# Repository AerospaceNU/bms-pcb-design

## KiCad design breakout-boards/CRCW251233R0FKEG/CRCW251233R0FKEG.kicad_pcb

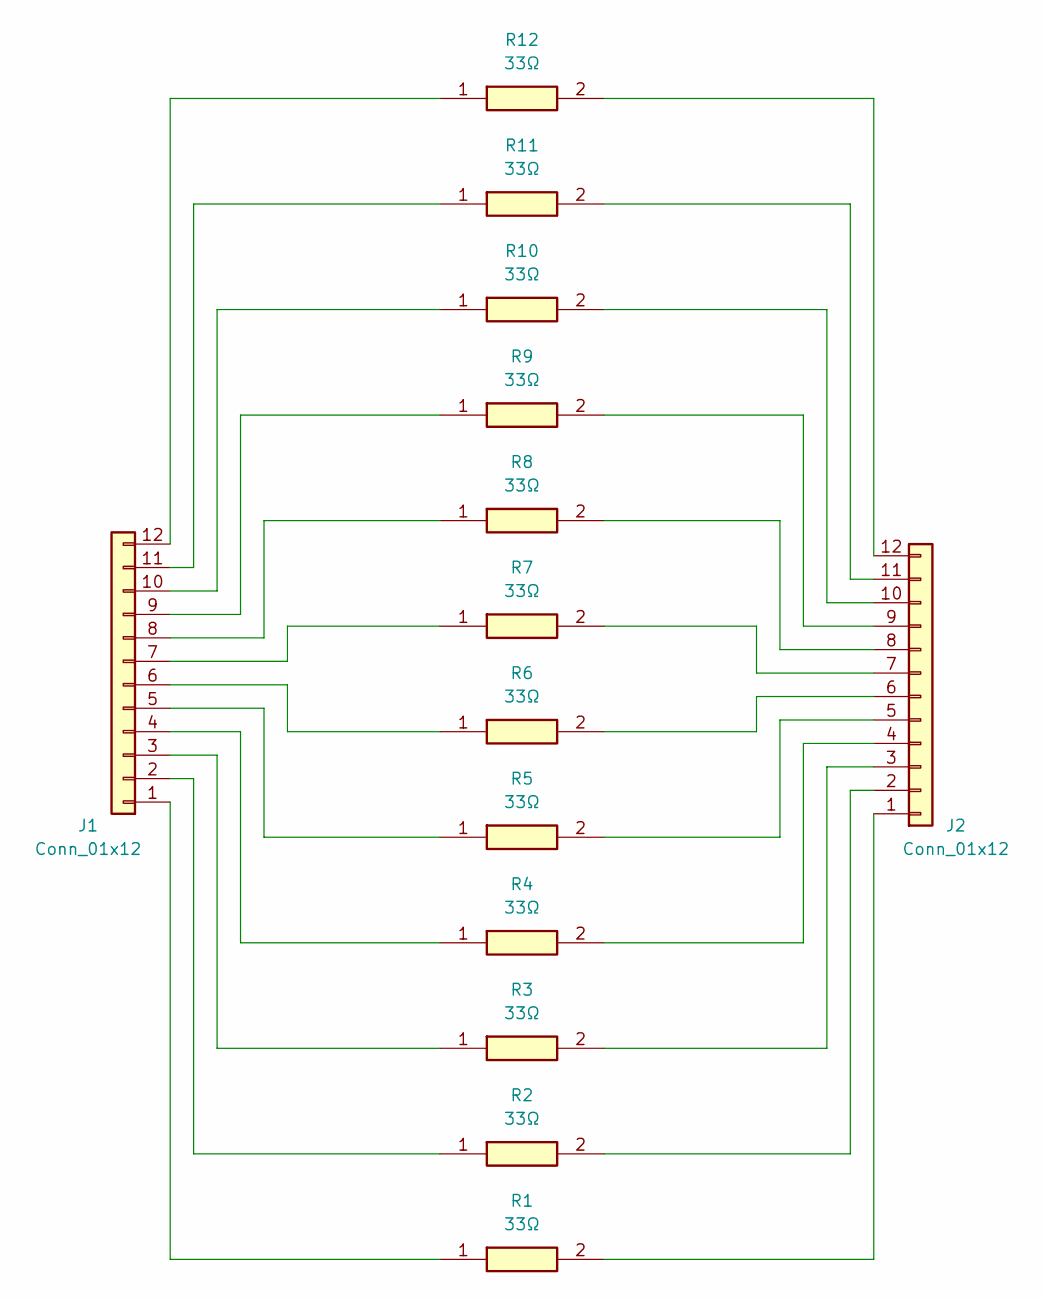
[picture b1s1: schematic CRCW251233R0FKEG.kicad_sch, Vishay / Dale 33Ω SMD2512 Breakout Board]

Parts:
J1, J2: Conn_01x12; PinSocket_1x12_P2.54mm_Vertical
R1, R2, R3, R4, R5, R6, R7, R8, R9, R10, R11, R12: 33Ω; RESC6332X70N; Manufacturer_Part_Number CRCW251233R0FKEG

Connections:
unnamed: J1.1, R1.1
unnamed: J1.2, R2.1
unnamed: J1.3, R3.1
unnamed: J1.4, R4.1
unnamed: J1.5, R5.1
unnamed: J1.6, R6.1
unnamed: J1.7, R7.1
unnamed: J1.8, R8.1
unnamed: J1.9, R9.1
unnamed: J1.10, R10.1
unnamed: J1.11, R11.1
unnamed: J1.12, R12.1
unnamed: J2.1, R1.2
unnamed: J2.2, R2.2
unnamed: J2.3, R3.2
unnamed: J2.4, R4.2
unnamed: J2.5, R5.2
unnamed: J2.6, R6.2
unnamed: J2.7, R7.2
unnamed: J2.8, R8.2
unnamed: J2.9, R9.2
unnamed: J2.10, R10.2
unnamed: J2.11, R11.2
unnamed: J2.12, R12.2

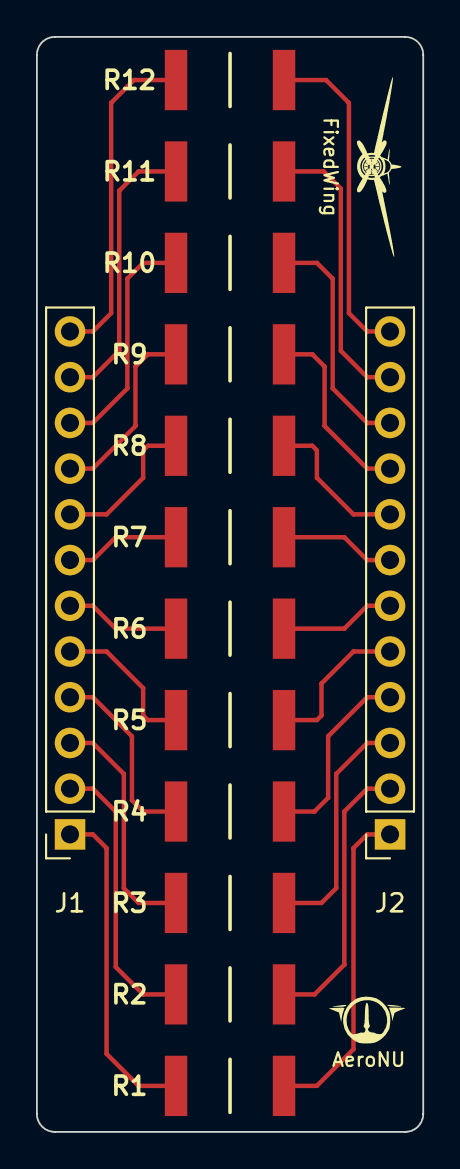
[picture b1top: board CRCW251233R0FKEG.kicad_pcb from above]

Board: 2 copper layers, 21.5 x 60.8 mm, 16 parts (0 on the bottom side), 24 nets.

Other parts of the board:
AeroNU: LOGO; AeroNU - Logo (Smol)
FixedWing: LOGO; FixedWing - Logo (Smol)

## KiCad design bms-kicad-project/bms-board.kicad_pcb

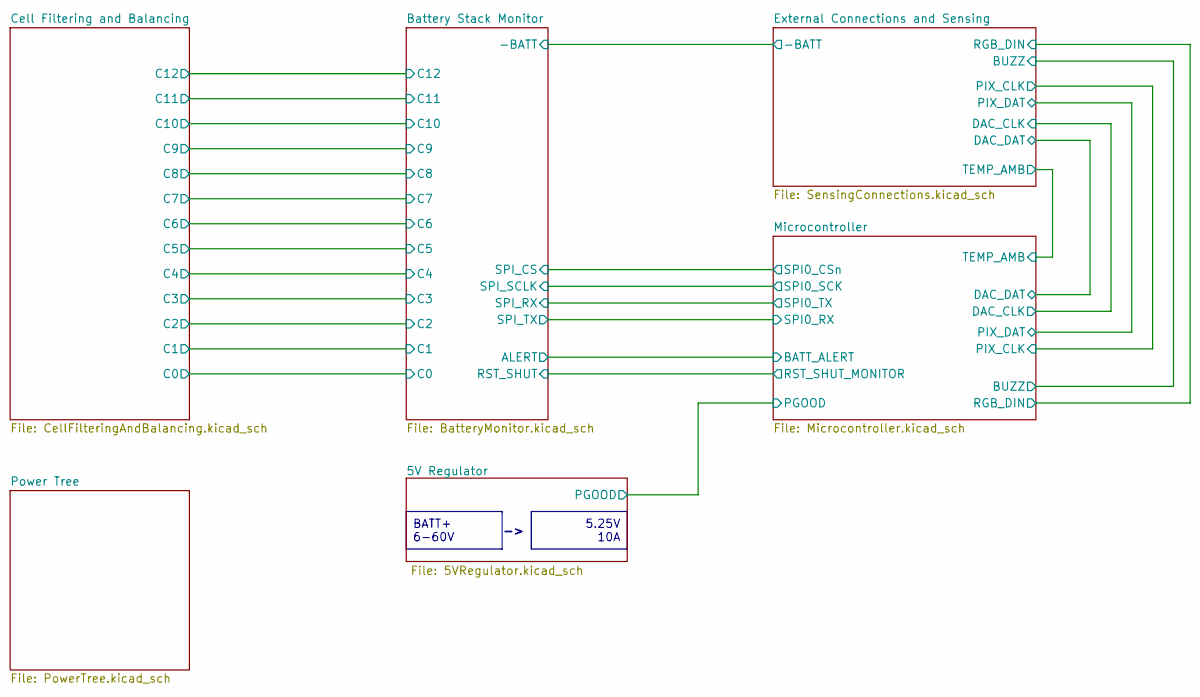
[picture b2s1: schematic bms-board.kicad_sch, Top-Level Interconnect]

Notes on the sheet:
BATT+ 6-60V
5.25V 10A

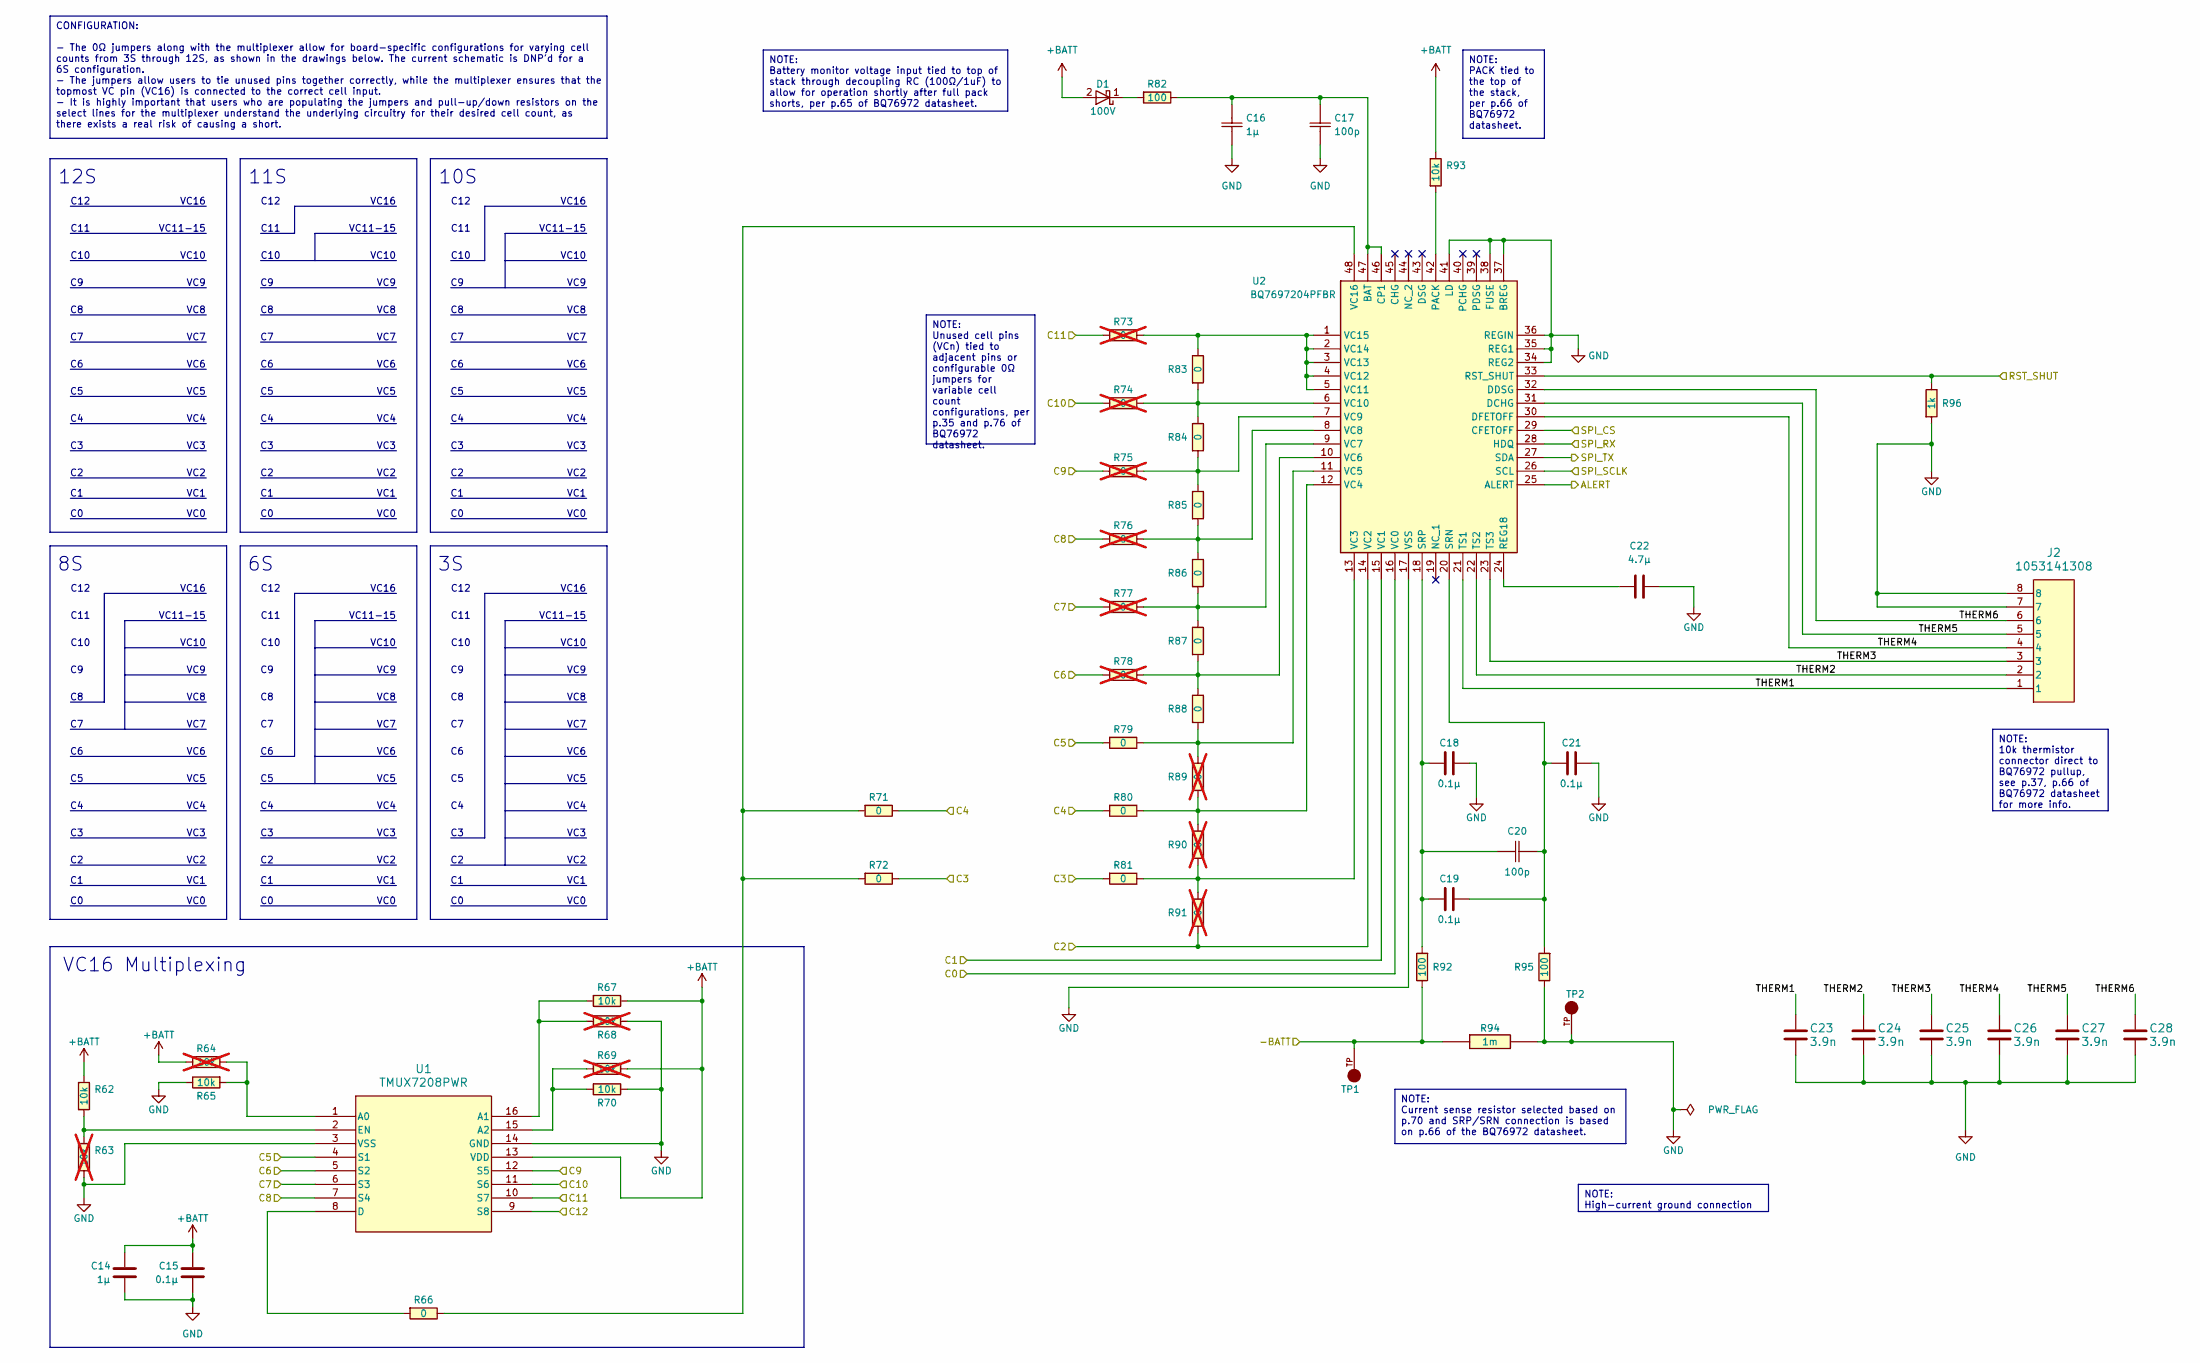
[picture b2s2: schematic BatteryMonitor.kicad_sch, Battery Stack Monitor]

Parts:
C14: 1µ; CAPC1608X90N; Manufacturer Part Number GCM188R71C105KA64D
C15, C18, C19, C21: 0.1µ; CAP_GCJ-18_MUR; Manufacturer Part Number GCJ188R72A104KA01D
C16: 1µ; CAP_CL31_SAM; Manufacturer Part Number CL31B105KCHNNNE
C17, C20: 100p; CAPC220145_88N_KEM; Manufacturer Part Number C0805C101J1GACTU
C22: 4.7µ; CAPC2012X145N; Manufacturer Part Number GCM21BC71E475KE36L
C23, C24, C25, C26, C27, C28: 3.9n; G-21_MUR; Manufacturer Part Number GRM2165C1H392JA01D
D1: 100V; D_SOD-123; Manufacturer Part Number BAS100AS_R1_00001
J2: 1053141308; CONN_SD-105314-100_08_MOL; Manufacturer Part Number 1053141308
R62, R65, R67, R70, R93: 10k; KOA_Speer-RK73H2A-0-0-MFG; power rating 0.125W; tolerance 1%; Manufacturer Part Number RK73H2ATTD1002F; digikey description RES 10K OHM 1% 1/4W 0805
R63, R64, R68, R69: 10k; KOA_Speer-RK73H2A-0-0-MFG; power rating 0.125W; tolerance 1%; Manufacturer Part Number RK73H2ATTD1002F; digikey description RES 10K OHM 1% 1/4W 0805; not fitted
R66, R71, R72, R79, R80, R81, R83, R84, R85, R86, R87, R88: 0; RES_CRCW_0805_VIS; Manufacturer Part Number CRCW08050000Z0EA
R73, R74, R75, R76, R77, R78, R89, R90, R91: 0; RES_CRCW_0805_VIS; Manufacturer Part Number CRCW08050000Z0EA; not fitted
R82, R92, R95: 100; RESC2012X50N; Mouser Part Number 71-CRCW0805-100-E3
R94: 1m; RES_5930R; Manufacturer Part Number SEWF5930F1L00P9
R96: 1k; RC0805N_YAG; Manufacturer Part Number RC0805FR-071KL
TP1, TP2: 5261; KEYSTONE_5261; PARTREV H
U1: TMUX7208PWR; TSSOP16-PW_TEX; Manufacturer Part Number TMUX7208PWR
U2: BQ7697204PFBR; QFP50P900X900X120-48N; Manufacturer Part Number BQ7697204PFBR; Mouser Part Number 595-BQ7697202PFBR

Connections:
+BATT: C14.2, C15.2, D1.2, R62.2, R64.2, R67.2, R69.2, R93.2, U1.13 (VDD); also elsewhere on the board
/Battery Stack Monitor/-BATT: R92.2, R94.1, TP1.TP; also elsewhere on the board
/Battery Stack Monitor/ALERT: U2.25 (ALERT); also elsewhere on the board
/Battery Stack Monitor/C0: U2.16 (VC0); also elsewhere on the board
/Battery Stack Monitor/C1: U2.15 (VC1); also elsewhere on the board
/Battery Stack Monitor/C2: R91.1, U2.14 (VC2); also elsewhere on the board
/Battery Stack Monitor/C3: R72.2, R81.1; also elsewhere on the board
/Battery Stack Monitor/C4: R71.2, R80.1; also elsewhere on the board
/Battery Stack Monitor/C5: R79.1, U1.4 (S1); also elsewhere on the board
/Battery Stack Monitor/C6: R78.1, U1.5 (S2); also elsewhere on the board
/Battery Stack Monitor/C7: R77.1, U1.6 (S3); also elsewhere on the board
/Battery Stack Monitor/C8: R76.1, U1.7 (S4); also elsewhere on the board
/Battery Stack Monitor/C9: R75.1, U1.12 (S5); also elsewhere on the board
/Battery Stack Monitor/C10: R74.1, U1.11 (S6); also elsewhere on the board
/Battery Stack Monitor/C11: R73.1, U1.10 (S7); also elsewhere on the board
/Battery Stack Monitor/C12: U1.9 (S8); also elsewhere on the board
/Battery Stack Monitor/RST_SHUT: R96.2, U2.33 (RST_SHUT); also elsewhere on the board
/Battery Stack Monitor/SPI_CS: U2.29 (CFETOFF); also elsewhere on the board
/Battery Stack Monitor/SPI_RX: U2.28 (HDQ); also elsewhere on the board
/Battery Stack Monitor/SPI_SCLK: U2.26 (SCL); also elsewhere on the board
/Battery Stack Monitor/SPI_TX: U2.27 (SDA); also elsewhere on the board
/Battery Stack Monitor/THERM1: C23.2, J2.1, U2.21 (TS1)
/Battery Stack Monitor/THERM2: C24.2, J2.2, U2.22 (TS2)
/Battery Stack Monitor/THERM3: C25.2, J2.3, U2.23 (TS3)
/Battery Stack Monitor/THERM4: C26.2, J2.4, U2.30 (DFETOFF)
/Battery Stack Monitor/THERM5: C27.2, J2.5, U2.31 (DCHG)
/Battery Stack Monitor/THERM6: C28.2, J2.6, U2.32 (DDSG)
GND: C14.1, C15.1, C16.1, C17.1, C18.2, C21.2, C22.2, C23.1, C24.1, C25.1, C26.1, C27.1, C28.1, J2.7, J2.8, R63.1, R65.2, R68.2, R70.2, R94.2, R95.2, R96.1, TP2.TP, U1.3 (VSS), U1.14 (GND), U2.17 (VSS), U2.34 (REG2), U2.35 (REG1), U2.36 (REGIN), U2.37 (BREG), U2.38 (FUSE), U2.41 (LD); also elsewhere on the board
unnamed: D1.1, R82.1
unnamed: R64.1, R65.1, U1.1 (A0)
unnamed: R67.1, R68.1, U1.16 (A1)
unnamed: R69.1, R70.1, U1.15 (A2)
unnamed: R66.1, U1.8 (D)
unnamed: R62.1, R63.2, U1.2 (EN)
unnamed: C16.2, C17.2, R82.2, U2.46 (CP1), U2.47 (BAT)
unnamed: R93.1, U2.42 (PACK)
unnamed: C22.1, U2.24 (REG18)
unnamed: C19.2, C20.1, C21.1, R95.1, U2.20 (SRN)
unnamed: C18.1, C19.1, C20.2, R92.1, U2.18 (SRP)
unnamed: R81.2, R90.1, R91.2, U2.13 (VC3)
unnamed: R80.2, R89.1, R90.2, U2.12 (VC4)
unnamed: R79.2, R88.1, R89.2, U2.11 (VC5)
unnamed: R78.2, R87.1, R88.2, U2.10 (VC6)
unnamed: R77.2, R86.1, R87.2, U2.9 (VC7)
unnamed: R76.2, R85.1, R86.2, U2.8 (VC8)
unnamed: R75.2, R84.1, R85.2, U2.7 (VC9)
unnamed: R74.2, R83.1, R84.2, U2.6 (VC10)
unnamed: R73.2, R83.2, U2.1 (VC15), U2.2 (VC14), U2.3 (VC13), U2.4 (VC12), U2.5 (VC11)
unnamed: R66.2, R71.1, R72.1, U2.48 (VC16)

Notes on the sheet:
NOTE: Unused cell pins (VCn) tied to adjacent pins or configurable 0Ω jumpers for variable cell count configurations, per p.35 and p.76 of BQ76972 datasheet.
NOTE: PACK tied to the top of the stack, per p.66 of BQ76972 datasheet.
NOTE: Battery monitor voltage input tied to top of stack through decoupling RC (100Ω/1uF) to allow for operation shortly after full pack shorts, per p.65 of BQ76972 datasheet.
NOTE: Current sense resistor selected based on p.70 and SRP/SRN connection is based on p.66 of the BQ76972 datasheet.
NOTE: High-current ground connection
CONFIGURATION: - The 0Ω jumpers along with the multiplexer allow for board-specific configurations for varying cell counts from 3S through 12S, as shown in the drawings below. The current schematic is DNP'd for a 6S configuration. - The jumpers allow users to tie unused pins together correctly, whi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
NOTE: 10k thermistor connector direct to BQ76972 pullup, see p.37, p.66 of BQ76972 datasheet for more info.
VC2
VC9
VC1
C10
12S
C12
VC10
VC3
VC16
C11
VC5
VC6
VC7
VC4
VC0
VC8
VC11-15
10S
VC16 Multiplexing
11S

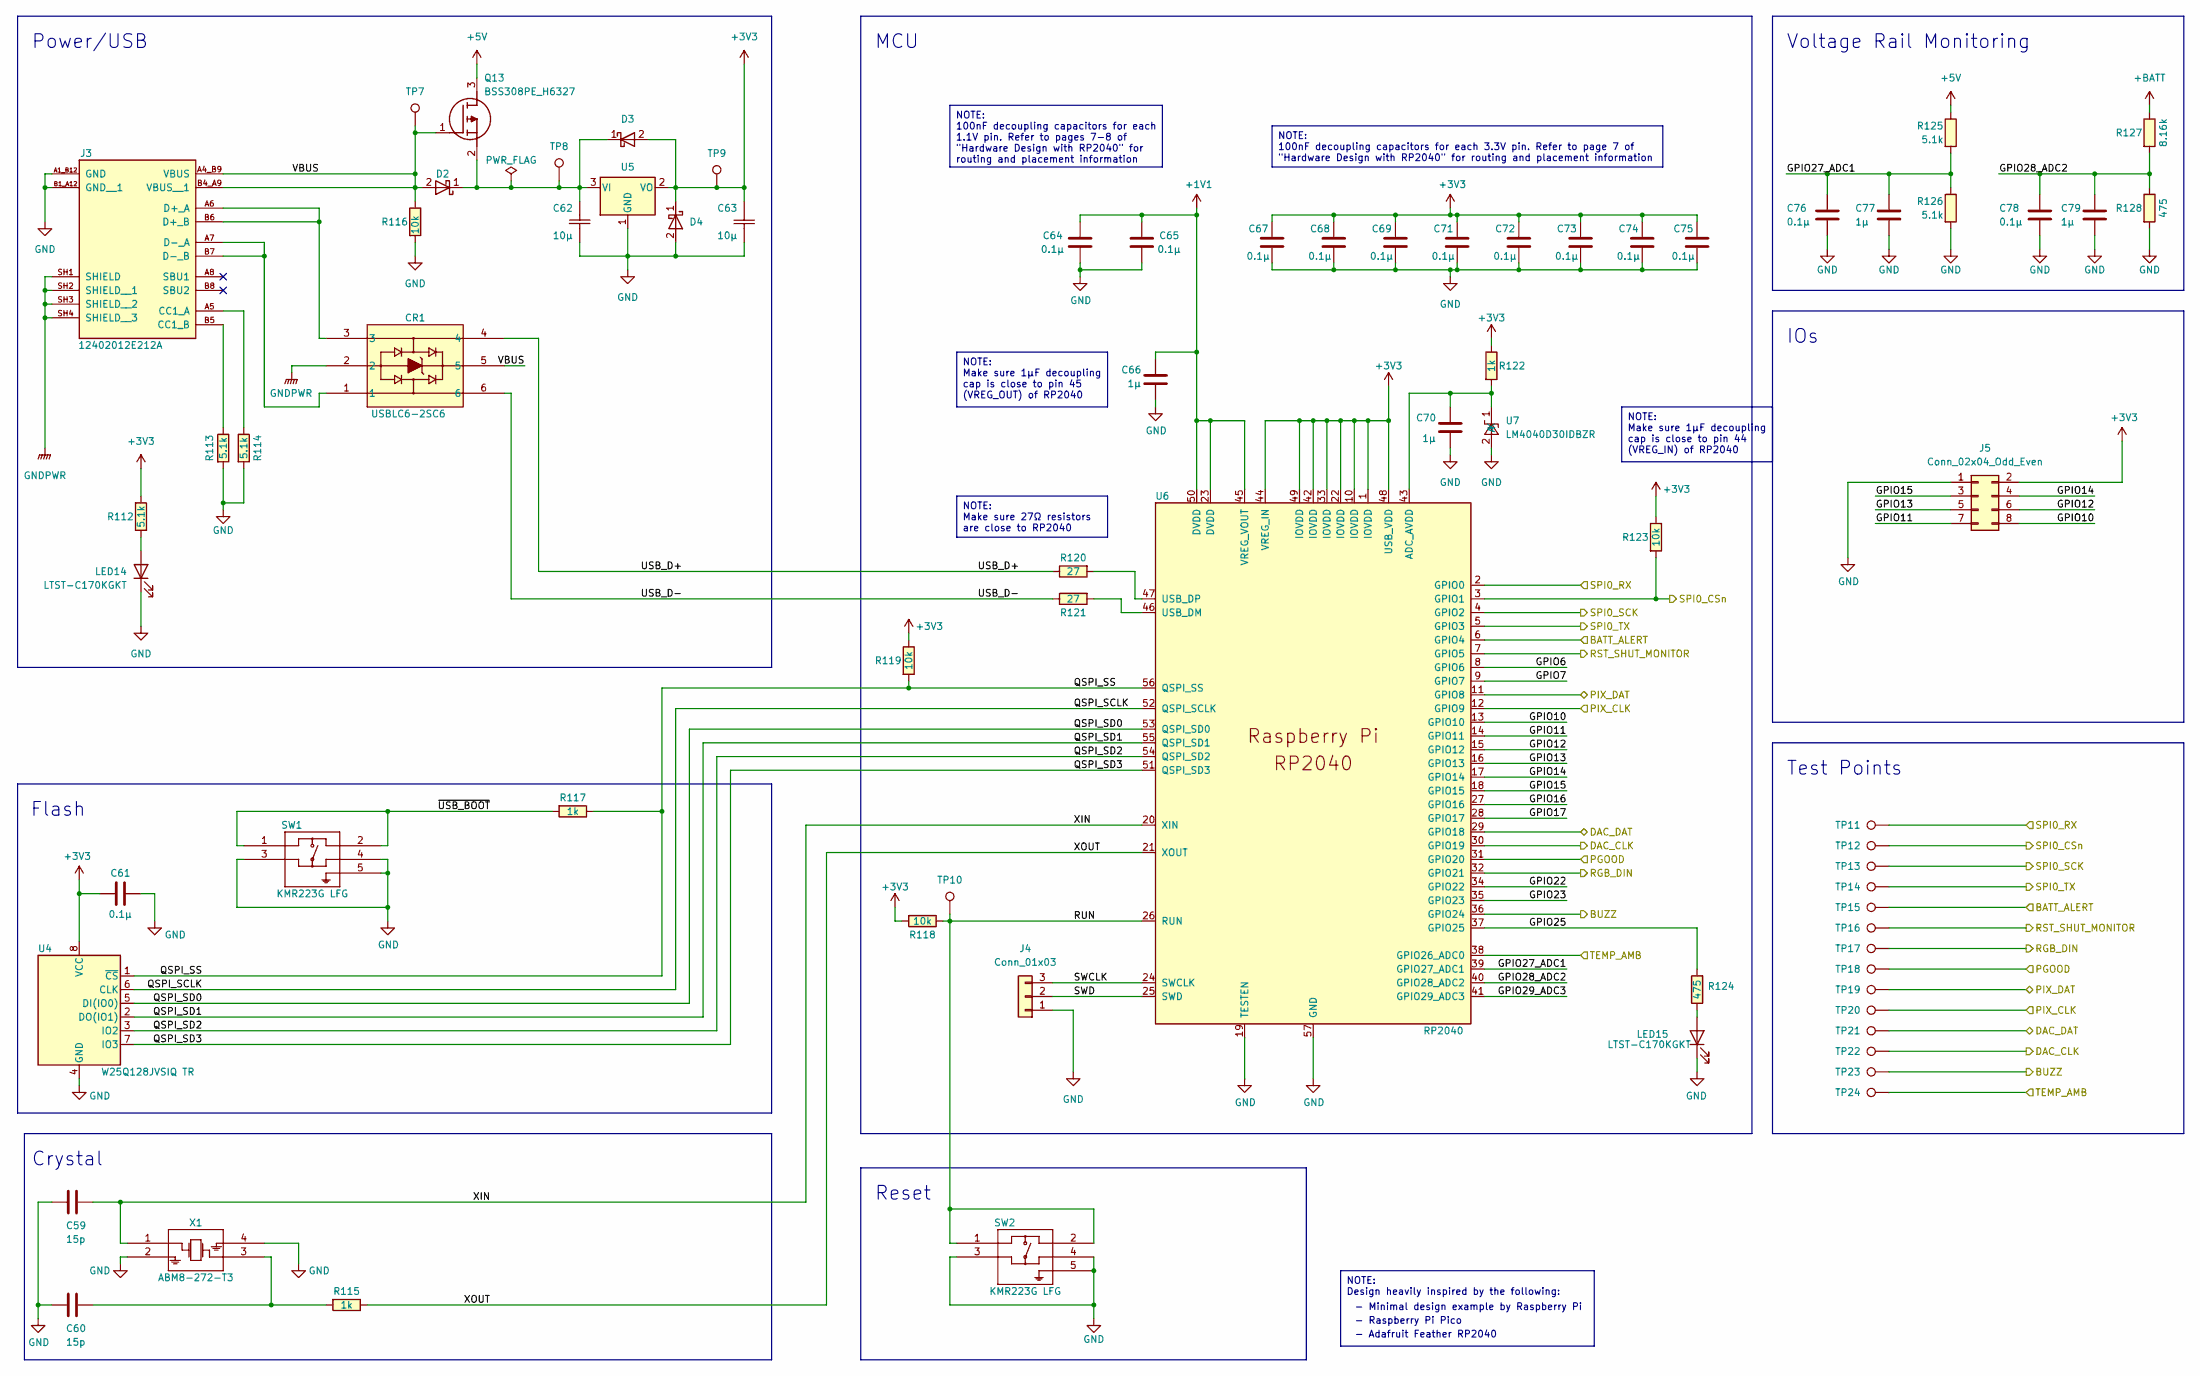
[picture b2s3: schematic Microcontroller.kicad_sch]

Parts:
C59, C60: 15p; CAPC2012X70; Manufacturer_Part_Number CC0805JPNPO9BN150
C61, C64, C65, C67, C68, C69, C71, C72, C73, C74, C75: 0.1µ; CAP_GCJ-18_MUR; Manufacturer_Part_Number GCJ188R72A104KA01D
C62, C63: 10µ; CAP_CL21B106KOQNNNE_SAM; Manufacturer Part Number CL21B106KOQNNNE
C66, C70, C77, C79: 1µ; CAPC1608X90N; Manufacturer Part Number GCM188R71C105KA64D
C76, C78: 0.1µ; CAP_GCJ-18_MUR; Manufacturer Part Number GCJ188R72A104KA01D
CR1: USBLC6-2SC6; SOT23-6L_STM; Manufacturer Part Number USBLC6-2SC6
D2, D3, D4: 100V; D_SOD-123; Manufacturer Part Number BAS100AS_R1_00001
J3: 12402012E212A; AMPHENOL_12402012E212A; PARTREV 4
J4: Conn_01x03; PinHeader_1x03_P2.54mm_Vertical
J5: Conn_02x04_Odd_Even; PinHeader_2x04_P2.54mm_Vertical
LED14, LED15: LTST-C170KGKT; LED_LTST-C170KGKT_LTO; Manufacturer Part Number LTST-C170KGKT
Q13: BSS308PE_H6327; SOT95P260X110-3N; Mouser Part Number 726-BSS308PEH6327
R112, R113, R114, R125, R126: 5.1k; RESC2012X60N; Manufacturer Part Number RC0805JR-075K1L
R115, R117: 1k; RC0805N_YAG; Manufacturer_Part_Number RC0805FR-071KL
R116, R118, R119, R123: 10k; KOA_Speer-RK73H2A-0-0-MFG; power rating 0.125W; tolerance 1%; Manufacturer Part Number RK73H2ATTD1002F; digikey description RES 10K OHM 1% 1/4W 0805
R120, R121: 27; RC0805N_YAG; Manufacturer_Part_Number RC0805FR-0727RL
R122: 1k; RC0805N_YAG; Manufacturer Part Number RC0805FR-071KL
R124, R128: 475; RESC2012X50N; Mouser Part Number 71-CRCW0805-475-E3
R127: 8.16k; RC0805N_YAG; Manufacturer Part Number RT0805BRD078K16L
SW1, SW2: KMR223G LFG; KMR2_G_CNK; Manufacturer_Part_Number KMR223GLFG
TP7, TP8, TP9, TP10, TP11, TP12, TP13, TP14, TP15, TP16, TP17, TP18, TP19, TP20, TP21, TP22, TP23, TP24: TestPoint_Pad_D1.0mm
U4: W25Q128JVSIQ TR; SOIC_208MIL_WIN; Manufacturer_Part_Number W25Q128JVSIQ TR
U5: NCP1117ST33T3G; SOT223-3_ONS; Manufacturer Part Number NCP1117ST33T3G
U6: RP2040; RP2040-QFN-56; Manufacturer_Part_Number SC0914(13)
U7: LM4040D30IDBZR; DBZ3_TEX
X1: ABM8-272-T3; ABM8-272-T3_ABR; Manufacturer_Part_Number ABM8-272-T3

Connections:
+1V1: C64.2, C65.2, C66.2, U6.23 (DVDD), U6.45 (VREG_VOUT), U6.50 (DVDD)
+3V3: C61.1, C63.2, C67.1, C68.1, C69.2, C71.1, C72.1, C73.1, C74.1, C75.1, D3.2, D4.1, J5.2, R112.1, R118.1, R119.2, R122.2, R123.2, TP9.1, U4.8 (VCC), U5.2 (VO), U6.1 (IOVDD), U6.10 (IOVDD), U6.22 (IOVDD), U6.33 (IOVDD), U6.42 (IOVDD), U6.44 (VREG_IN), U6.48 (USB_VDD), U6.49 (IOVDD); also elsewhere on the board
+5V: Q13.3 (D), R125.2; also elsewhere on the board
+BATT: R127.1; also elsewhere on the board
/5V Regulator/PGOOD: TP18.1, U6.31 (GPIO20); also elsewhere on the board
/Battery Stack Monitor/ALERT: TP15.1, U6.6 (GPIO4); also elsewhere on the board
/Battery Stack Monitor/RST_SHUT: TP16.1, U6.7 (GPIO5); also elsewhere on the board
/Battery Stack Monitor/SPI_CS: R123.1, TP12.1, U6.3 (GPIO1); also elsewhere on the board
/Battery Stack Monitor/SPI_RX: TP14.1, U6.5 (GPIO3); also elsewhere on the board
/Battery Stack Monitor/SPI_SCLK: TP13.1, U6.4 (GPIO2); also elsewhere on the board
/Battery Stack Monitor/SPI_TX: TP11.1, U6.2 (GPIO0); also elsewhere on the board
/External Connections and Sensing/BUZZ: TP23.1, U6.36 (GPIO24); also elsewhere on the board
/External Connections and Sensing/DAC_CLK: TP22.1, U6.30 (GPIO19); also elsewhere on the board
/External Connections and Sensing/DAC_DAT: TP21.1, U6.29 (GPIO18); also elsewhere on the board
/External Connections and Sensing/PIX_CLK: TP20.1, U6.12 (GPIO9); also elsewhere on the board
/External Connections and Sensing/PIX_DAT: TP19.1, U6.11 (GPIO8); also elsewhere on the board
/External Connections and Sensing/RGB_DIN: TP17.1, U6.32 (GPIO21); also elsewhere on the board
/External Connections and Sensing/TEMP_AMB: TP24.1, U6.38 (GPIO26_ADC0); also elsewhere on the board
/Microcontroller/GPIO6: U6.8 (GPIO6)
/Microcontroller/GPIO7: U6.9 (GPIO7)
/Microcontroller/GPIO10: J5.8, U6.13 (GPIO10)
/Microcontroller/GPIO11: J5.7, U6.14 (GPIO11)
/Microcontroller/GPIO12: J5.6, U6.15 (GPIO12)
/Microcontroller/GPIO13: J5.5, U6.16 (GPIO13)
/Microcontroller/GPIO14: J5.4, U6.17 (GPIO14)
/Microcontroller/GPIO15: J5.3, U6.18 (GPIO15)
/Microcontroller/GPIO16: U6.27 (GPIO16)
/Microcontroller/GPIO17: U6.28 (GPIO17)
/Microcontroller/GPIO22: U6.34 (GPIO22)
/Microcontroller/GPIO23: U6.35 (GPIO23)
/Microcontroller/GPIO25: R124.1, U6.37 (GPIO25)
/Microcontroller/GPIO27_ADC1: C76.2, C77.2, R125.1, R126.2, U6.39 (GPIO27_ADC1)
/Microcontroller/GPIO28_ADC2: C78.2, C79.2, R127.2, R128.2, U6.40 (GPIO28_ADC2)
/Microcontroller/GPIO29_ADC3: U6.41 (GPIO29_ADC3)
/Microcontroller/QSPI_SCLK: U4.6 (CLK), U6.52 (QSPI_SCLK)
/Microcontroller/QSPI_SD0: U4.5 (DI(IO0)), U6.53 (QSPI_SD0)
/Microcontroller/QSPI_SD1: U4.2 (DO(IO1)), U6.55 (QSPI_SD1)
/Microcontroller/QSPI_SD2: U4.3 (IO2), U6.54 (QSPI_SD2)
/Microcontroller/QSPI_SD3: U4.7 (IO3), U6.51 (QSPI_SD3)
/Microcontroller/QSPI_SS: R117.2, R119.1, U4.1 (~CS), U6.56 (QSPI_SS)
/Microcontroller/RUN: R118.2, SW2.1, SW2.2, TP10.1, U6.26 (RUN)
/Microcontroller/SWCLK: J4.3, U6.24 (SWCLK)
/Microcontroller/SWD: J4.2, U6.25 (SWD)
/Microcontroller/USB_D+: CR1.4, R120.2
/Microcontroller/USB_D-: CR1.6, R121.2
/Microcontroller/VBUS: CR1.5, D2.2, J3.A4_B9 (VBUS), J3.B4_A9 (VBUS__1), Q13.1 (G), R116.2, TP7.1
/Microcontroller/XIN: C59.2, U6.20 (XIN), X1.1
/Microcontroller/XOUT: R115.2, U6.21 (XOUT)
/Microcontroller/~USB_BOOT: R117.1, SW1.1, SW1.2
GND: C59.1, C60.1, C61.2, C62.2, C63.1, C64.1, C65.1, C66.1, C67.2, C68.2, C69.1, C70.1, C71.2, C72.2, C73.2, C74.2, C75.2, C76.1, C77.1, C78.1, C79.1, CR1.2, D4.2, J3.A1_B12 (GND), J3.B1_A12 (GND__1), J3.SH1 (SHIELD), J3.SH2 (SHIELD__1), J3.SH3 (SHIELD__2), J3.SH4 (SHIELD__3), J4.1, J5.1, LED14.1 (K), LED15.1 (K), R113.1, R114.1, R116.1, R126.1, R128.1, SW1.3, SW1.4, SW1.5, SW2.3, SW2.4, SW2.5, U4.4 (GND), U5.1 (GND), U6.19 (TESTEN), U6.57 (GND), U7.2 (A), X1.2, X1.4; also elsewhere on the board
unnamed: C60.2, R115.1, X1.3
unnamed: J3.A5 (CC1_A), R114.2
unnamed: J3.B5 (CC1_B), R113.2
unnamed: CR1.3, J3.A6 (D+_A), J3.B6 (D+_B)
unnamed: CR1.1, J3.A7 (D-_A), J3.B7 (D-_B)
unnamed: LED14.2 (A), R112.2
unnamed: LED15.2 (A), R124.2
unnamed: C62.1, D2.1, D3.1, Q13.2 (S), TP8.1, U5.3 (VI)
unnamed: C70.2, R122.1, U6.43 (ADC_AVDD), U7.1 (K)
unnamed: R121.1, U6.46 (USB_DM)
unnamed: R120.1, U6.47 (USB_DP)

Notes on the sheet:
NOTE: Design heavily inspired by the following:
NOTE: Make sure 1μF decoupling cap is close to pin 45 (VREG_OUT) of RP2040
NOTE: 100nF decoupling capacitors for each 3.3V pin. Refer to page 7 of "Hardware Design with RP2040" for routing and placement information
NOTE: Make sure 1μF decoupling cap is close to pin 44 (VREG_IN) of RP2040
NOTE: 100nF decoupling capacitors for each 1.1V pin. Refer to pages 7-8 of "Hardware Design with RP2040" for routing and placement information
NOTE: Make sure 27Ω resistors are close to RP2040
IOs
Power/USB
Crystal
- Raspberry Pi Pico
- Adafruit Feather RP2040
- Minimal design example by Raspberry Pi
Voltage Rail Monitoring
MCU
Test Points
Reset
Flash

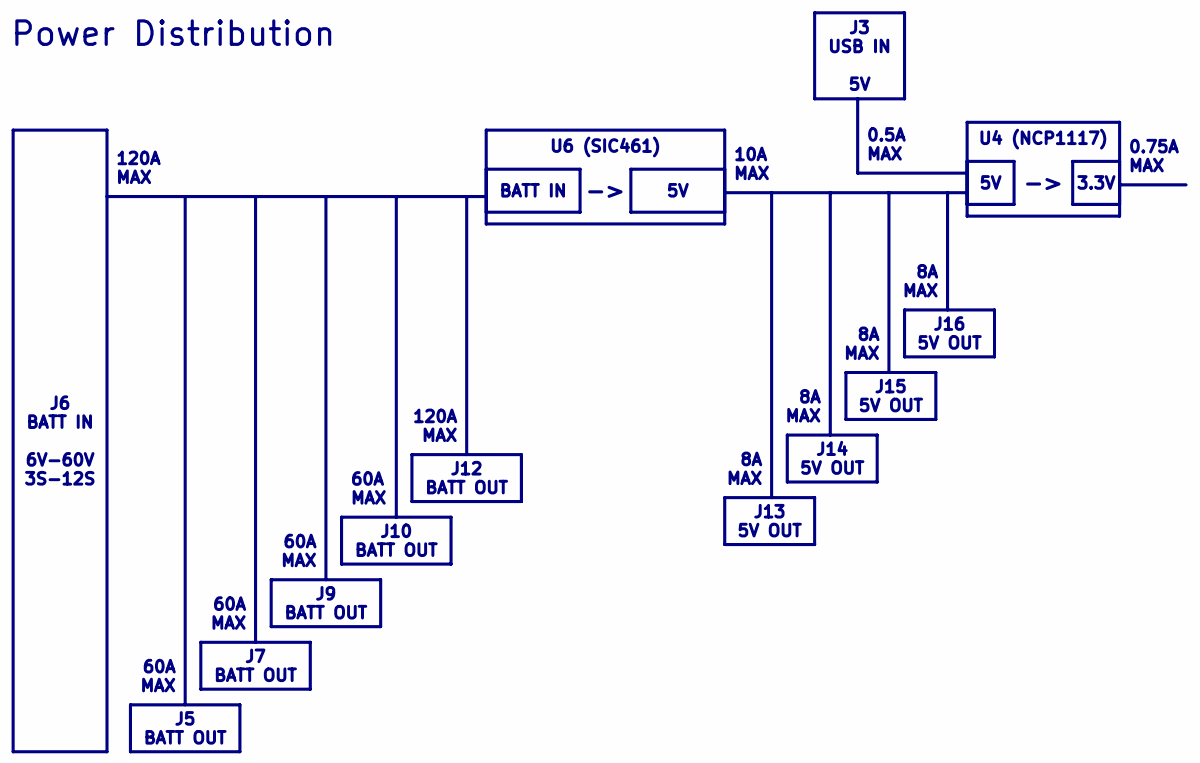
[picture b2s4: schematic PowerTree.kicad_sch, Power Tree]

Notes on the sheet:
J3 USB IN 5V
J6 BATT IN 6V-60V 3S-12S
J14 5V OUT
U6 (SIC461)
J10 BATT OUT
BATT IN
U4 (NCP1117)
J9 BATT OUT
3.3V
J16 5V OUT
J12 BATT OUT
J5 BATT OUT
J7 BATT OUT
J15 5V OUT
J13 5V OUT
8A MAX
10A MAX
0.5A MAX
60A MAX
Power Distribution
0.75A MAX
120A MAX
